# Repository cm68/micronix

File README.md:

for a blast from the past, type:

 make test

 you now are running the recovered 1.4 shell and can do a lot
 including: (this builds the kernel)

	cd /usr/src/sys
	make

or, for a quite strange experience,

    src/usersim/sim bin/man sh | less

	(run the simulated z80 micronix man program on sh, and pipe it to linux less)

---------------------

three version numbers turn up in here and they do not mean the same
thing.  this tree is released as micronix 2.0, which is the number the
kernel prints in its banner and the number the distribution disks in
dist/ are named for.  1.4 is the distribution userland - the shell and
the commands in disks/dist, recovered from the original disks.  1.61 is
where the kernel source was recovered from: it is the provenance of that
source and not what the tree now is.

micronix 2.0 is a substantially enhanced kernel, not the 1.61 kernel
with a new number on it.  the boards are discovered at boot and each
driver is a module placed only if its card answers, so one kernel boots
the SS1, the Wunderbus and the MultIO; the buffer cache hashes its
headers and keeps the data in segments behind a window, with room for
over a hundred buffers against 1.61's fifteen; the task maps are
per-process and a switch no longer copies one, and each process has its
own u page and stack; exec builds its arguments straight into the new
image, and execve adds an environment; and the system call table has
grown dup2, ftruncate, ioctl, reboot, execve and select.
src/micronix/sys/FEATURES-2.md is the full account, with the counts
taken from the two kernels.

three additions since the release notes are worth calling out.  rshd is
the big one: the machine can now be logged into from the network and
not only copied from - an rsh from another machine reaches a shell on a
pty, authenticated by /etc/hosts.equiv and ~/.rhosts, so micronix is no
longer only a client.  ioctl now reaches character devices as well as
block ones: a terminal's status is the two requests TIOCGETA and
TIOCSETA, so gtty and stty are at last only library wrappers over them,
and the network card's socket face is its own NET* requests.  select is
there too - crippled but functional: it waits on a mask of up to
sixteen descriptors and returns the ones that can be read, with no
timeout and no write set, and sees only ttys and the network sockets; a
deadline is an alarm(2), which returns it with EINTR.  with these,
micronix is close to seventh edition.  the difference that stands out
is the inode, which keeps two timestamps, access and modify, where V7
keeps a third, change time.

micronix 2.0 - release notes, 21 oct 2026

this is the first release of micronix in 42 years.  it is a complete
source release, with significantly enhanced functionality and much
higher performance on the same hardware:

	an entirely new C compiler and tool chain.  it exploits the Z80
	chip for significant speed and space improvements over the
	Whitesmith's compiler.  in addition, it accepts most of ANSI C.

	up to 128K of ram is used as a buffer cache, greatly reducing
	disk i/o.

	it exploits the mpz80 hardware contexts to make context switches
	much cheaper.

	exec now allows a large number of arguments, limited by memory
	size.

	unix 7th edition changes: ioctl, lseek, dup2, O_APPEND,
	ftruncate, environment variables, bourne shell, make, less and
	many others.

	a network interface has been added supporting an ESP32 connection.
	the ESP32 runs tcp/ip and wifi; rcp copies files over rsh, rshd
	serves rsh into the box, and inetd runs rlogin, telnet and ftp
	there.

	the console is chosen at boot: the morrow multio ACE or the compupro
	SS1's 2651.  wunderbus ACEs and the serial lines give additional
	terminals, so the machine is multi-user over serial.

	halt and reboot commands are added.

	format utilities running natively for all supported disk
	controllers.

	modular device drivers: all block device drivers share a single
	4k segment, so many different drivers can be loaded on the same
	kernel.

	automatic interrupt probing: all disk controllers can be strapped
	to any unused S100 VI line, and it will be automatically
	detected.

	automatic detection of interrupt controllers: the morrow multio,
	wunderbus I/O and compupro system support are all supported.

	the tool chain is self-hosting: the source tree rebuilds itself
	natively, and the second generation is byte-identical to the first
	(make verify).

	drivers for the following controllers have been added, along with
	boot rom support if running the included mon5.0:

		morrow hdc/dma, dj/dma, hdca
		compupro disk1, disk2, disk3
		s100computers.com dual ide, scsi

	disk partitioning.  micronix only used up to 32MB of a disk.  a
	new disk labeling facility made disks self-describing, so the
	kernel no longer needs to know disk geometry.

the source tree, the build instructions and the 1.4 userland / 1.61
kernel provenance are in this file.  make test runs the recovered 1.4
shell; the d1 simulator and usersim run the system without the hardware,
and the 2.0 distribution media are under dist/ and attached to the 2.0 release.
the tree is Apache 2.0 (LICENSE); the Z80 instruction tables in
src/include/z80.h carry the zlib/libpng notice in LICENSE.z80.

---------------------

Morrow Designs Micronix and tools					updated 21 Oct 2026

directories:

filesystem:
	built by the top level makefile from the distribution disks
	this is used by the usersim to run against
	it holds the source and rebuilds itself natively (cd /usr/src; make)

disks:
	floppy images recovered from the net, version 1.4 and 1.3

wslib:
	the whitesmith's libraries, burst apart and disassembled - gone
	from the top level; what remains is under attic/wslib and
	attic/wssrc, with the rest of the retired material

src/micronix:
	the source tree for things that are to be built natively, including
    libraries, commands and the kernel.
	this is gradually being fleshed out with replacements for the micronix
	utilities that I don't have source for, namely all of them.
	notable additions:
		a v7 make
		the PWB yacc, lex, expr and fd2, and 2.11's awk
		tar, msh (the shell), less, diff and mv
		an in-memory, ansi-only, vi subset derived from stevie
		2.11's ls and cp
		a working pwd, rm, mknod
		the ccc compiler, described below
	
src/micronix/lib:
	additions and replacements for the whitesmith's library.
		
src/micronix/sys:
	kernel source, recovered from a micronix 1.61 build (see the version
	note above), with include files.
	the formatting of the original source was really quirky and archaic,
	so I re-indented it to a more K&R like style.
	it is NOT ansi, and compiles with ccc (see below).

src/micronix/stand:
	ghidra-driven rewrite of the cold boot loaders for the kernel

src/micronix/include:
	include files rejiggered to make porting from v6 and v7 easier

src/tools:
	file system checkers, dumper and extractor
	object file tools, including an overachieving nm and 
	a rootin' tootin' fire-breathing disassembler that knows about
	hitech objects, whitesmith's objects, and com files, does
	code tracing, and allows a symbol file to be fed in. 

src/lib:
	libraries for file system, disassembly, and random utility
	
src/usersim:
	micronix user mode simulator, including upm, the cp/m emulator.
	it is quite solid.

	special files are symlinks that name the device - bdev(maj,min) or
	cdev(maj,min) - and the block devices are real: mount() and umount()
	go through the host fslib, with -D <devdir> pointing at a directory of
	bdev(maj,min) links to images.  mkfs, fsck, icheck and the rest open
	the raw device the same way.

	build it on any random unix box (centos is baseline),
	and run:  sim

src/hwsim:
	a hardware level mpz80 simulator that boots the micronix kernel.
	it includes the ability to load+run the monitor roms, load symbol
	tables, has an ICE-like debugger with breakpoints, single step,
	disassembler, and so on.  furthermore, it has a modular architecture
	that allows plugging in different chip simulators.

	it runs cp/m and boots micronix to a shell, with interrupt controller,
	trapping, memory mapping, and disk reading and writing for the disk
	controllers (djdma, hddma, hdca, ide, ncr5380, and CompuPro's
	disk1/disk2/disk3), the ND network card, the SS1 and the MultIO.
	the card list is the DRIVERS line in src/hwsim/d1/GNUmakefile.

	there's a means for importing and exporting data to cp/m via the
	inp: and out: devices in pip, so hex files can be shipped to get
	programs in and out.

	the djdma simulator reads IMD files directly, and writes produce
	a delta file that is loaded at the next startup, so there's no
	modification of the original IMD.  the imd utility can generate
	a merged IMD file that contains any changes.

src/include:
	library include files for the emulation

ccc:
	this tree's own c compiler, written from scratch - cpp, c0, c1, peep,
	asz and ld, the passes in src/micronix/libexec and the driver and
	friends in src/micronix/cmd.  it cross builds on the host (mxccc) and
	natively inside micronix (ccc), and targets both micronix and cp/m -
	-m micronix links libu, -m cpm links libcpm, and both link the one
	pure libc.  everything in this tree builds with it.

extra/v6, extra/v7, extra/2.11
	oh, yeah.  this is the real mc-coy.  this is useful for reference and
	tool source grabbing.  the porting to micronix is simple, if tedious.
	the include files are subtly different.

publicdocs:
	almost everything I could find on the micronix hardware - flattened from
	extra/docs - and miscellaneous morrow stuff that may be useful.

extra/decomp:
	a decompiler that knows about code flow, system calls, and
        with the goal of generating recompilable C.  very much a WIP.
	probably throw away now that ghidra exists.

extra/sim:
	a bunch of 8 bit simulators for cribbing ideas/code from.
	these all are licensed by thier original authors, so...

build prerequisites
-------------------

the tree builds with the host's make and gcc, but nearly all of it is
built for 32 bits: src/GNUmakefile.inc sets MACHINE = -m32, and the
host tools the cross toolchain runs are 32-bit as well.  a host with no
32-bit target and no 32-bit libraries will not build it.  on
debian/ubuntu:

	apt install build-essential gcc-multilib libc6-dev-i386 \
		lib32ncurses-dev bison

	build-essential		gcc, make and the C library
	gcc-multilib		the -m32 target and its runtime
	libc6-dev-i386		32-bit libc headers and crt files
	lib32ncurses-dev	the 32-bit curses the simulators and
				host tools link with -lcurses
	bison			generates src/tools/zmac.c from zmac.y

on a red hat family host the equivalents are gcc, make, glibc-devel.i686,
ncurses-devel.i686 and bison, with the 32-bit packages from a multilib
channel.  centos is the baseline the tree was developed against.

one build is separate from the tree's own.  the ESP32 network card
firmware in src/micronix/stand/nic is a PlatformIO project
(platformio.ini, the arduino framework, the esp32doit-devkit-v1 board);
it is not part of the top level make.  install PlatformIO Core -
"pipx install platformio", or the installer from platformio.org - so
that pio is on PATH, then

	make -C src/micronix/stand/nic		# pio run

the ESP32 tool chain and the arduino framework are downloaded on the
first build.  flashing (make upload) wants the board's USB-UART as
/dev/ttyUSB* or /dev/ttyACM*; on debian/ubuntu that means membership in
the dialout group.

xterm is not needed to build, but the hardware simulator's -c option
puts each simulated terminal in one; without it d1 uses the controlling
terminal.  it is a separate package ("apt install xterm" on
debian/ubuntu) and needs an X display.

running micronix in simulation
------------------------------

two simulators, two experiences.

usersim (src/usersim) is the easy one: it hosts micronix's system calls
on linux and runs against filesystem/, no simulated hardware, no disk
images.  build once, then

	make
	src/usersim/sim

hwsim (src/hwsim/d1) is the real machine - the Morrow MPZ80, the monitor
rom, the real kernel, every controller in its card list - and it boots
micronix to a '#' shell on a simulated disk.  it is the one that needs
setup.

the short boot, from a standing start:

	make
	cd src/micronix && make bootstrap
	make -C src/micronix/stand/boot bootimgs

	disks/hdinstall/create_vol myvol	# a bootable volume
	disks/hdinstall/boot_vol myvol		# boot it, console in an xterm

boot_vol passes -c 0x70c: boot the hdcdma straight, skip the monitor,
and put the console in an xterm of its own.  the boot block mkfs left on
cylinder 0 loads /micronix.

the performance build is the same simulator with the debug machinery
compiled out - d1p, or d1 -F - and it runs at roughly a 30 mhz z80,
which makes it pleasant to use rather than watch.  everything works at
that speed: multi-user logins, a compile on one terminal while ps runs
on another.

the full install, from the distribution - build the diskettes, provision
a two-disk machine, and install it automatically:

	dist/create_dist 8		# 9 diskettes into dist/mx2.0-8-*.IMD
	disks/hdinstall/build_dist	# two 34 MB volumes + the install script
	disks/hdinstall/dist_boot	# boot and install all 9, watch the xterm

build_dist and dist_boot drive the install through /dev/mediachg, the
out-of-band media changer: the guest program chg swaps the floppy images
in the simulator without an eject syscall, and the install script loads
and copies each diskette in turn.  the grammar is
src/micronix/sys/MEDIACHG.md.

the whole flow, the disk-label model and the boot loaders are in
docs/INSTALLATION.md, disks/hdinstall/README and sys/DISKLABEL.md.

the provisioning tool
---------------------

a command-line tool, src/tools/hwsim (built by make at the top of the
tree), that drives the simulator the way the per-card scripts do by
hand.  the simulated platforms are defined in sim.json at the top of the
tree: each entry under "sims" names the emulator and kernel, the monitor
and level-1 boot roms, the boot device, the console and clock
configuration, the wiring profile, the root and swap device tokens, and
the volumes - controller, unit, geometry and image for each.  the
"mediasets" in the same file name the floppy IMD sets, and -f names a
different platform file.

a sim is a collection of volumes, and a volume is a disk on a controller
- its geometry and its card, not a role.  the verbs:

	hwsim format <sim>		mnix initialize (geometry label)
	hwsim partition <sim>		mnix label (default slice table)
	hwsim mkfs <sim>		mnix mkfs (filesystem + boot)
	hwsim boot <sim>		launch d1/d1p from config + volumes
	hwsim add <sim> <controller> <unit> <geometry> <image>
	hwsim del <sim> <controller>:<unit>
	hwsim list			the sims defined in the file
	hwsim show <sim>		one sim's definition

root and swap are the kernel's setdev arguments, named as device tokens
(hdcdma:0a), not volume attributes; -c packs boot, nomon, the xterm mask
and the clock from named fields.  the common case - build and boot the
sample two-disk sim (q540-dual):

	src/tools/hwsim format q540-dual	# initialize both m40 volumes
	src/tools/hwsim partition q540-dual	# the default slice table
	src/tools/hwsim mkfs q540-dual		# filesystem + boot on slice a
	src/tools/hwsim boot q540-dual		# d1p, packed -c, both disks wired

the full design - the json schema and the bit tables - is
src/tools/PROVISION.md.  build_dist and dist_boot are the same thing done
by hand, and the media changer (sys/MEDIACHG.md) is how a boot's floppies
get loaded.

this github is prettily referenced in my cybernecromancy site:

https://retro.zen-room.org/morrow-micronix/user-mode-simulator

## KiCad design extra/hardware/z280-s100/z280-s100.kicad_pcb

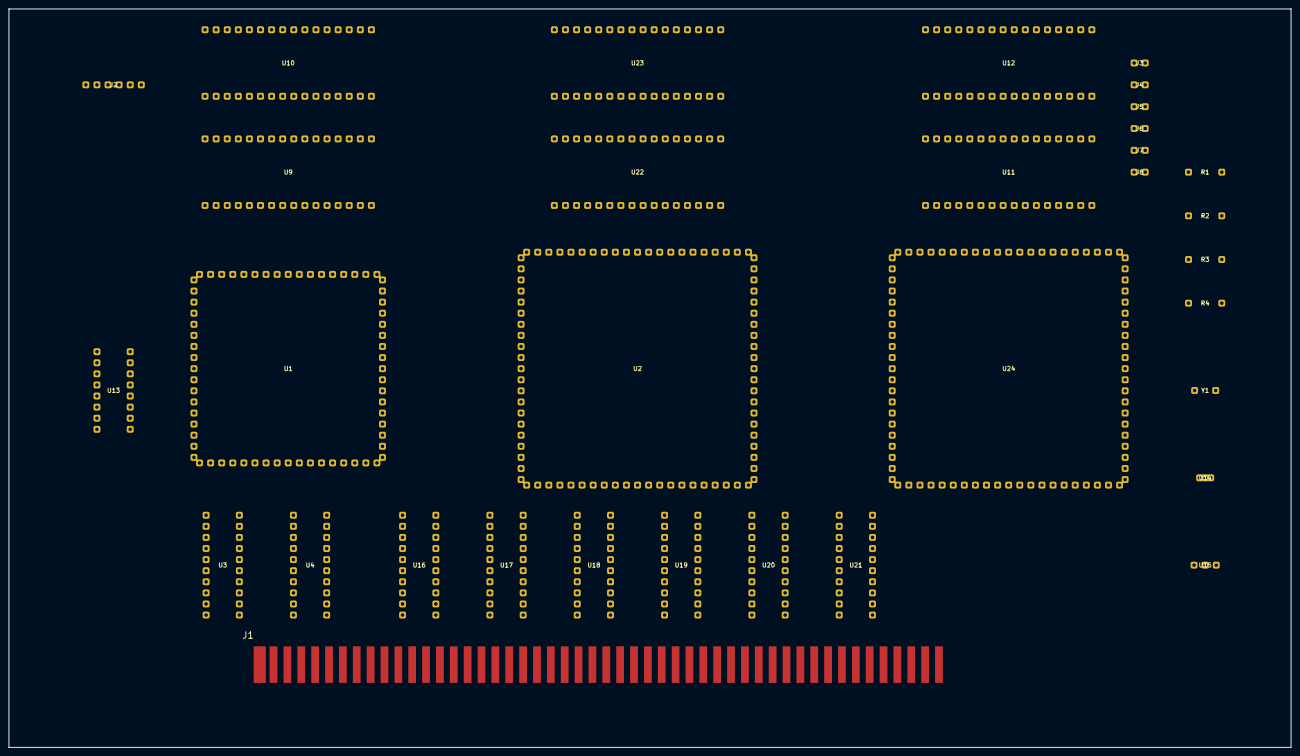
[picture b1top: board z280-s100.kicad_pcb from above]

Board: 2 copper layers, 293.6 x 169.1 mm, 33 parts (0 on the bottom side), 174 nets, no tracks yet.

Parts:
J1: S-100 edge; S100_MALE
J2: JTAG (1x6); HDR-6
J3: JP VPP; HDR-2
J4: JP A15; HDR-2
J5: JP A16; HDR-2
J6: JP A17/VDD; HDR-2
J7: JP PGM; HDR-2
J8: JP VDD; HDR-2
R1: 1k pRDY; HDR-2
R2: 1k XRDY; HDR-2
R3: 1k SLAVE_ONLY; HDR-2
R4: 1k SIXTN; HDR-2
U1: Z280 (PLCC-68); PLCC-68-SKT
U2: ATF1508 control; PLCC-84-SKT
U3: 74HC573 lo; DIP-20
U4: 74HC573 hi; DIP-20
U9: SRAM bank0 even; DIP-32
U10: SRAM bank0 odd; DIP-32
U11: 27SF020 even; DIP-32
U12: 27SF020 odd; DIP-32
U13: MAX232; DIP-16
U14: DS1813 reset; HDR-3
U15: 7805; HDR-3
U16: 74HCT245 addr0; DIP-20
U17: 74HCT245 addr1; DIP-20
U18: 74HCT245 addr2; DIP-20
U19: 74HCT245 status; DIP-20
U20: 74HCT245 control; DIP-20
U21: 74HCT245 pHLDA; DIP-20
U22: SRAM bank1 even; DIP-32
U23: SRAM bank1 odd; DIP-32
U24: ATF1508 data; PLCC-84-SKT
Y1: 24 MHz crystal; HDR-2

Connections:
+5V: J2.6, J3.2, J7.2, J8.2, R1.1, R2.1, R4.1, U1.18, U1.19, U1.34, U2.3, U2.13, U2.26, U2.38, U2.43, U2.53, U2.66, U2.78, U3.20, U4.20, U9.28, U10.28, U13.16, U14.3, U15.3, U16.20, U17.20, U18.20, U19.20, U20.20, U21.1, U21.20, U22.28, U23.28, U24.3, U24.13, U24.26, U24.38, U24.43, U24.53, U24.66, U24.78
+8V: J1.1, J1.51, U15.1
A16: J4.2, U1.5, U9.32, U10.32, U18.2, U22.32, U23.32, U24.2
A17: J5.2, U1.6, U9.31, U10.31, U18.3, U22.31, U23.31, U24.4
A18: J6.2, U1.8, U9.30, U10.30, U18.4, U22.30, U23.30, U24.5
A19: U1.9, U9.29, U10.29, U18.5, U22.29, U23.29, U24.6
A20: U1.45, U18.6, U24.8
A21: U1.59, U18.7, U24.9
A22: U1.66, U18.8, U24.10
A23: U1.7, U18.9, U24.11
AD0: U1.40, U3.2, U10.11, U12.13, U23.11, U24.28
AD1: U1.42, U3.3, U10.12, U12.14, U23.12, U24.29
AD2: U1.43, U3.4, U10.13, U12.15, U23.13, U24.30
AD3: U1.44, U3.5, U10.15, U12.17, U23.15, U24.31
AD4: U1.54, U3.6, U10.16, U12.18, U23.16, U24.33
AD5: U1.57, U3.7, U10.17, U12.19, U23.17, U24.34
AD6: U1.60, U3.8, U10.18, U12.20, U23.18, U24.35
AD7: U1.61, U3.9, U10.19, U12.21, U23.19, U24.36
AD8: U1.62, U4.2, U9.11, U11.13, U22.11, U24.37
AD9: U1.64, U4.3, U9.12, U11.14, U22.12, U24.39
AD10: U1.65, U4.4, U9.13, U11.15, U22.13, U24.40
AD11: U1.67, U4.5, U9.15, U11.17, U22.15, U24.41
AD12: U1.68, U4.6, U9.16, U11.18, U22.16, U24.44
AD13: U1.2, U4.7, U9.17, U11.19, U22.17, U24.45
AD14: U1.3, U4.8, U9.18, U11.20, U22.18, U24.46
AD15: U1.4, U4.9, U9.19, U11.21, U22.19, U24.48
BANK: U2.33, U24.73
BYTE_SEL: U2.73, U16.2, U24.16
CPLD_pDBIN: U2.51, U20.4
CPLD_pHLDA: U2.54, U21.2
CPLD_pSTVAL: U2.50, U20.3
CPLD_pSYNC: U2.49, U20.2
CPLD_pWR: U2.52, U20.5
CPLD_sHLTA: U2.46, U19.7
CPLD_sINP: U2.41, U19.4
CPLD_sINTA: U2.45, U19.6
CPLD_sMEMR: U2.39, U19.2
CPLD_sOUT: U2.44, U19.5
CPLD_sWO: U2.40, U19.3
CPLD_sXTRQ: U2.48, U19.8
FLASH_A15: J4.1, U11.3, U12.3
FLASH_A16: J5.1, U11.2, U12.2
FLASH_A17: J6.1, U11.30, U12.30
FLASH_CE: U2.61, U11.22, U12.22
FLASH_OE: U2.63, U11.24, U12.24
FLASH_PGM: J7.1, U11.31, U12.31
FLASH_VDD: J8.1, U11.32, U12.32
FLASH_VPP: J3.1, U11.1, U12.1
FLASH_WIN: U2.31, U24.70
GND: J1.20, J1.50, J1.53, J1.70, J1.100, J2.5, R3.1, U1.1, U1.35, U1.51, U1.53, U2.7, U2.19, U2.32, U2.42, U2.47, U2.59, U2.72, U2.82, U3.1, U3.10, U4.1, U4.10, U9.14, U10.14, U11.16, U12.16, U13.15, U14.1, U15.2, U16.10, U17.10, U18.10, U19.10, U20.10, U21.3, U21.4, U21.5, U21.6, U21.7, U21.8, U21.9, U21.10, U21.19, U22.14, U23.14, U24.7, U24.19, U24.32, U24.42, U24.47, U24.59, U24.72, U24.82
JTAG_CHAIN: U2.71, U24.14
JTAG_TCK: J2.1, U2.62, U24.62
JTAG_TDI: J2.3, U2.14
JTAG_TDO: J2.4, U24.71
JTAG_TMS: J2.2, U2.23, U24.23
LA0: U2.27, U3.12
LA1: U2.28, U3.13, U11.12, U12.12, U16.3
LA2: U2.29, U3.14, U11.11, U12.11, U16.4
LA3: U3.15, U9.8, U10.8, U11.10, U12.10, U16.5, U22.8, U23.8
LA4: U3.16, U9.7, U10.7, U11.9, U12.9, U16.6, U22.7, U23.7
LA5: U3.17, U9.6, U10.6, U11.8, U12.8, U16.7, U22.6, U23.6
LA6: U3.18, U9.5, U10.5, U11.7, U12.7, U16.8, U22.5, U23.5
LA7: U3.19, U9.4, U10.4, U11.6, U12.6, U16.9, U22.4, U23.4
LA8: U4.12, U9.3, U10.3, U11.5, U12.5, U17.2, U22.3, U23.3
LA9: U4.13, U9.25, U10.25, U11.27, U12.27, U17.3, U22.25, U23.25
LA10: U4.14, U9.24, U10.24, U11.26, U12.26, U17.4, U22.24, U23.24
LA11: U4.15, U9.21, U10.21, U11.23, U12.23, U17.5, U22.21, U23.21
LA12: U4.16, U9.23, U10.23, U11.25, U12.25, U17.6, U22.23, U23.23
LA13: U4.17, U9.2, U10.2, U11.4, U12.4, U17.7, U22.2, U23.2
LA14: U4.18, U9.26, U10.26, U11.28, U12.28, U17.8, U22.26, U23.26
LA15: U4.19, U9.1, U10.1, U11.29, U12.29, U17.9, U22.1, U23.1
LATCH_LE: U2.64, U3.11, U4.11
MASTER_ACTIVE: U2.69, U24.12
MASTER_WRITE: U2.70, U24.15
MEM_CE0: U2.55, U9.20, U10.20
MEM_CE1: U2.56, U22.20, U23.20
MEM_OE: U2.57, U9.22, U10.22, U22.22, U23.22
MEM_WE_H: U2.60, U10.27, U23.27
MEM_WE_L: U2.58, U9.27, U22.27
NC: U13.7, U13.8, U13.9, U13.10, U13.12
S100_A0: J1.79, U16.11
S100_A1: J1.80, U16.12
S100_A2: J1.81, U16.13
S100_A3: J1.31, U16.14
S100_A4: J1.30, U16.15
S100_A5: J1.29, U16.16
S100_A6: J1.82, U16.17
S100_A7: J1.83, U16.18
S100_A8: J1.84, U17.11
S100_A9: J1.34, U17.12
S100_A10: J1.37, U17.13
S100_A11: J1.87, U17.14
S100_A12: J1.33, U17.15
S100_A13: J1.85, U17.16
S100_A14: J1.86, U17.17
S100_A15: J1.32, U17.18
S100_A16: J1.16, U18.11
S100_A17: J1.17, U18.12
S100_A18: J1.15, U18.13
S100_A19: J1.59, U18.14
S100_A20: J1.61, U18.15
S100_A21: J1.62, U18.16
S100_A22: J1.63, U18.17
S100_A23: J1.64, U18.18
S100_ADSB: J1.22, U24.22
S100_A_DIR: U16.1, U17.1, U18.1, U24.75
S100_A_OE: U16.19, U17.19, U18.19, U24.74
S100_CDSB: J1.19, U24.27
S100_C_OE: U20.19, U24.77
S100_DI0: J1.95, U24.58
S100_DI1: J1.94, U24.60
S100_DI2: J1.41, U24.61
S100_DI3: J1.42, U24.63
S100_DI4: J1.91, U24.64
S100_DI5: J1.92, U24.65
S100_DI6: J1.93, U24.67
S100_DI7: J1.43, U24.68
S100_DO0: J1.36, U24.49
S100_DO1: J1.35, U24.50
S100_DO2: J1.88, U24.51
S100_DO3: J1.89, U24.52
S100_DO4: J1.38, U24.54
S100_DO5: J1.39, U24.55
S100_DO6: J1.40, U24.56
S100_DO7: J1.90, U24.57
S100_DODSB: J1.23, U24.24
S100_HOLD: J1.74, U2.20
S100_INT: J1.73, U2.17
S100_NMI: J1.12, U2.18
S100_SC_DIR: U19.1, U20.1, U24.79
S100_SDSB: J1.18, U24.25
S100_SIXTN: J1.60, R4.2, U2.24, U24.83
S100_S_OE: U19.19, U24.76
S100_XRDY: J1.3, R2.2, U2.22, U24.81
S100_pDBIN: J1.78, U20.13
S100_pHLDA: J1.26, U21.11
S100_pRDY: J1.72, R1.2, U2.21, U24.80
S100_pSTVAL: J1.25, U20.12
S100_pSYNC: J1.76, U20.11
S100_pWR: J1.77, U20.14
S100_sHLTA: J1.48, U19.16
S100_sINP: J1.46, U19.13
S100_sINTA: J1.96, U19.15
S100_sMEMR: J1.47, U19.11, U24.18
S100_sOUT: J1.45, U19.14
S100_sWO: J1.97, U19.12, U24.20
S100_sXTRQ: J1.58, U19.17, U24.21
SLAVE: U2.68, U24.1
SLAVE_ONLY: R3.2, U2.25
SRAM_A0: U2.65, U9.10, U10.10, U22.10, U23.10
SRAM_A1: U2.67, U9.9, U10.9, U22.9, U23.9
SRAM_WIN: U2.30, U24.69
XFR16: U2.74, U24.17
XTALI: U1.50, Y1.1
XTALO: U1.49, Y1.2
Z_AS: U1.27, U2.1
Z_BUSACK: U1.31, U2.15
Z_BUSREQ: U1.28, U2.37
Z_BW: U1.10, U2.5
Z_CLK: U1.47, U2.83
Z_DS: U1.24, U2.2
Z_IE: U1.17, U2.11
Z_INT: U1.37, U2.35
Z_NMI: U1.39, U2.36
Z_OE: U1.16, U2.12
Z_RESET: U1.38, U2.16, U14.2
Z_RW: U1.12, U2.4
Z_RXD: U1.48, U13.13
Z_ST0: U1.14, U2.6
Z_ST1: U1.15, U2.8
Z_ST2: U1.21, U2.9
Z_ST3: U1.22, U2.10
Z_TXD: U1.46, U13.11
Z_WAIT: U1.29, U2.34
